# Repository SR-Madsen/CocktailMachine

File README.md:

# Cocktail Machine
Contains the code and PCB used for the actual implementation of the STM32F4-based cocktail machine.

The DiscoveryDemo folder contains a TouchGFX demo used on the STM32F769 Discovery Board from ST.

Documentation, including a system report written in LaTeX, can be found in the Documentation folder.

## Overview
A block diagram overview of the system is shown below.

## Hardware
The PCB has been designed with inspiration from ST's discovery board.

## Software
A preliminary GUI template is shown below. This has been implemented in TouchGFX.

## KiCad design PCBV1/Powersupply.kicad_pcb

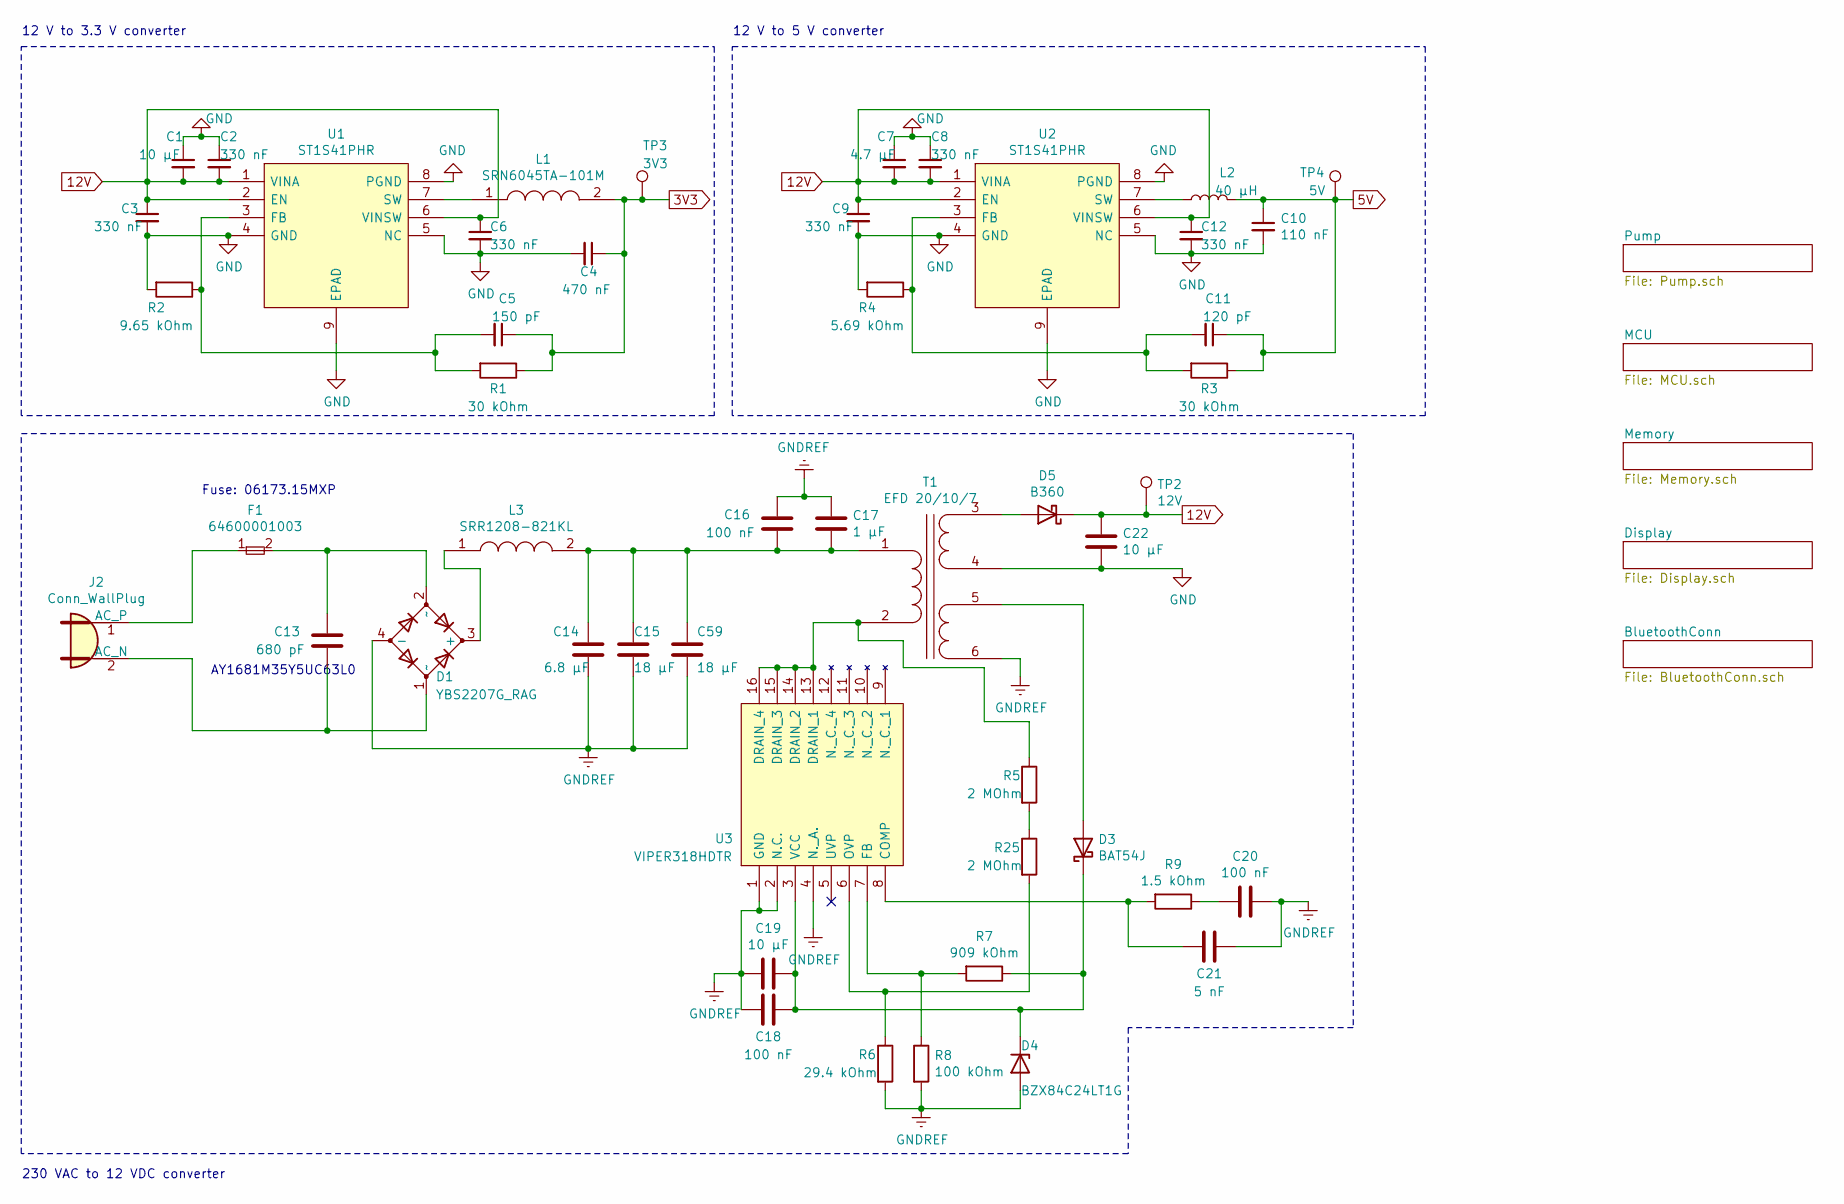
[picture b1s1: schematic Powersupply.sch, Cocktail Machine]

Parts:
C1, C19, C22: 10 µF; C_1206_3216Metric
C2, C3, C6, C8, C9, C12: 330 nF; C_0603_1608Metric
C4: 470 nF; C_0603_1608Metric
C5: 150 pF; C_0603_1608Metric
C7: 4.7 µF; C_0805_2012Metric
C10: 110 nF; C_0603_1608Metric
C11: 120 pF; C_0603_1608Metric
C13: 680 pF; C_Disc_D8.0mm_W5.0mm_P10.00mm
C14: 6.8 µF; CP_Radial_D10.0mm_P5.00mm
C15, C59: 18 µF; CP_Radial_D12.5mm_P5.00mm
C16: 100 nF; C_1210_3225Metric
C17: 1 µF; C_Rect_L24.0mm_W10.1mm_P22.50mm_MKT
C18, C20: 100 nF; C_0603_1608Metric
C21: 5 nF; C_0603_1608Metric
D1: YBS2207G_RAG; Mouser Part Number 821-YBS2207GRAG
D3: BAT54J; D_SOD-323F
D4: BZX84C24LT1G; D_SOT-23_ANK
D5: B360; D_SMC
F1: 64600001003; Mouser Part Number 576-64600001003
J2: Conn_WallPlug; PinHeader_1x02_P2.54mm_Vertical
L1: SRN6045TA-101M; Mouser Part Number 652-SRN6045TA-101M
L2: 40 µH; L_Bourns-SRN4018
L3: SRR1208-821KL; Mouser Part Number 652-SRR1208-821KL
R1, R3: 30 kOhm; R_0603_1608Metric
R2: 9.65 kOhm; R_0603_1608Metric
R4: 5.69 kOhm; R_0603_1608Metric
R5, R25: 2 MOhm; R_1206_3216Metric
R6: 29.4 kOhm; R_0603_1608Metric
R7: 909 kOhm; R_0603_1608Metric
R8: 100 kOhm; R_0603_1608Metric
R9: 1.5 kOhm; R_0603_1608Metric
T1: EFD 20/10/7; EFD_20_10_7
TP2: 12V; TestPoint_Pad_D2.0mm
TP3: 3V3; TestPoint_Pad_D2.0mm
TP4: 5V; TestPoint_Pad_D2.0mm
U1, U2: ST1S41PHR; Manufacturer_Part_Number ST1S41PHR
U3: VIPER318HDTR; Manufacturer_Part_Number VIPER318HDTR

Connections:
3V3: C4.1, C5.1, L1.2, R1.1, TP3.1; also elsewhere on the board
5V: C10.1, C11.1, L2.2, R3.1, TP4.1; also elsewhere on the board
12V: C1.2, C2.2, C3.1, C6.1, C7.2, C8.2, C9.1, C12.1, C22.1, D5.1 (K), TP2.1, U1.1 (VINA), U1.2 (EN), U1.6 (VINSW), U2.1 (VINA), U2.2 (EN), U2.6 (VINSW); also elsewhere on the board
GND: C1.1, C2.1, C3.2, C4.2, C6.2, C7.1, C8.1, C9.2, C10.2, C12.2, C22.2, R2.2, R4.2, T1.4 (SB), U1.4 (GND), U1.5 (NC), U1.8 (PGND), U1.9 (EPAD), U2.4 (GND), U2.5 (NC), U2.8 (PGND), U2.9 (EPAD); also elsewhere on the board
GNDREF: C14.2, C15.2, C16.1, C17.1, C18.2, C19.2, C20.1, C21.1, C59.2, D1.4 (-), D4.2 (A), R6.2, R8.2, T1.6 (SD), U3.1 (GND), U3.2 (N.C.), U3.4 (N._A.)
unnamed: C5.2, R1.2, R2.1, U1.3 (FB)
unnamed: C11.2, R3.2, R4.1, U2.3 (FB)
unnamed: C13.1, D1.2 (~~), F1.2
unnamed: C13.2, D1.1 (~~), J2.2 (AC_N)
unnamed: C14.1, C15.1, C16.2, C17.2, C59.1, L3.2, T1.1 (AA)
unnamed: C18.1, C19.1, D3.1 (K), D4.1 (K), R7.1, U3.3 (VCC)
unnamed: C20.2, R9.1
unnamed: C21.2, R9.2, U3.8 (COMP)
unnamed: D1.3 (+), L3.1
unnamed: D3.2 (A), T1.5 (SC)
unnamed: D5.2 (A), T1.3 (SA)
unnamed: F1.1, J2.1 (AC_P)
unnamed: L1.1, U1.7 (SW)
unnamed: L2.1, U2.7 (SW)
unnamed: R5.1, T1.2 (AB), U3.13 (DRAIN_1), U3.14 (DRAIN_2), U3.15 (DRAIN_3), U3.16 (DRAIN_4)
unnamed: R7.2, R8.1, U3.7 (FB)
unnamed: R5.2, R25.1
unnamed: R6.1, R25.2, U3.6 (OVP)

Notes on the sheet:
12 V to 3.3 V converter
12 V to 5 V converter
Fuse: 06173.15MXP
AY1681M35Y5UC63L0
230 VAC to 12 VDC converter

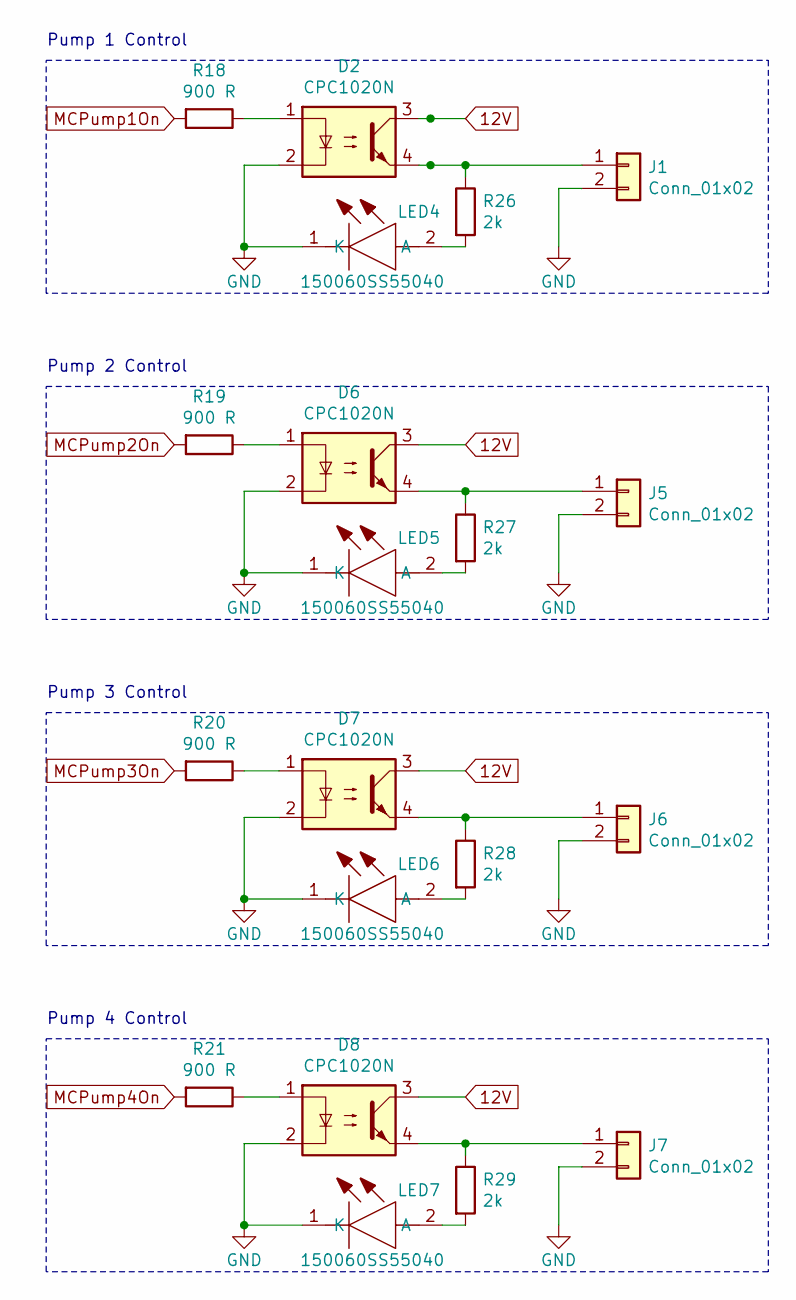
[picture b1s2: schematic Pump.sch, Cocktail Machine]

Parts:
D2, D6, D7, D8: CPC1020N; Mouser Part Number 849-CPC1020N
J1, J5, J6, J7: Conn_01x02; PinHeader_1x02_P2.54mm_Horizontal
LED4, LED5, LED6, LED7: 150060SS55040; Mouser Part Number 710-150060SS55040
R18, R19, R20, R21: 900 R; R_0603_1608Metric
R26, R27, R28, R29: 2k; R_0603_1608Metric

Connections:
12V: D2.3, D6.3, D7.3, D8.3; also elsewhere on the board
GND: D2.2, D6.2, D7.2, D8.2, J1.2, J5.2, J6.2, J7.2, LED4.1 (K), LED5.1 (K), LED6.1 (K), LED7.1 (K); also elsewhere on the board
MCPump1On: R18.2; also elsewhere on the board
MCPump2On: R19.2; also elsewhere on the board
MCPump3On: R20.2; also elsewhere on the board
MCPump4On: R21.2; also elsewhere on the board
unnamed: D2.1, R18.1
unnamed: D2.4, J1.1, R26.1
unnamed: D6.1, R19.1
unnamed: D6.4, J5.1, R27.1
unnamed: D7.1, R20.1
unnamed: D7.4, J6.1, R28.1
unnamed: D8.1, R21.1
unnamed: D8.4, J7.1, R29.1
unnamed: LED4.2 (A), R26.2
unnamed: LED5.2 (A), R27.2
unnamed: LED6.2 (A), R28.2
unnamed: LED7.2 (A), R29.2

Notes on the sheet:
Pump 1 Control
Pump 2 Control
Pump 3 Control
Pump 4 Control

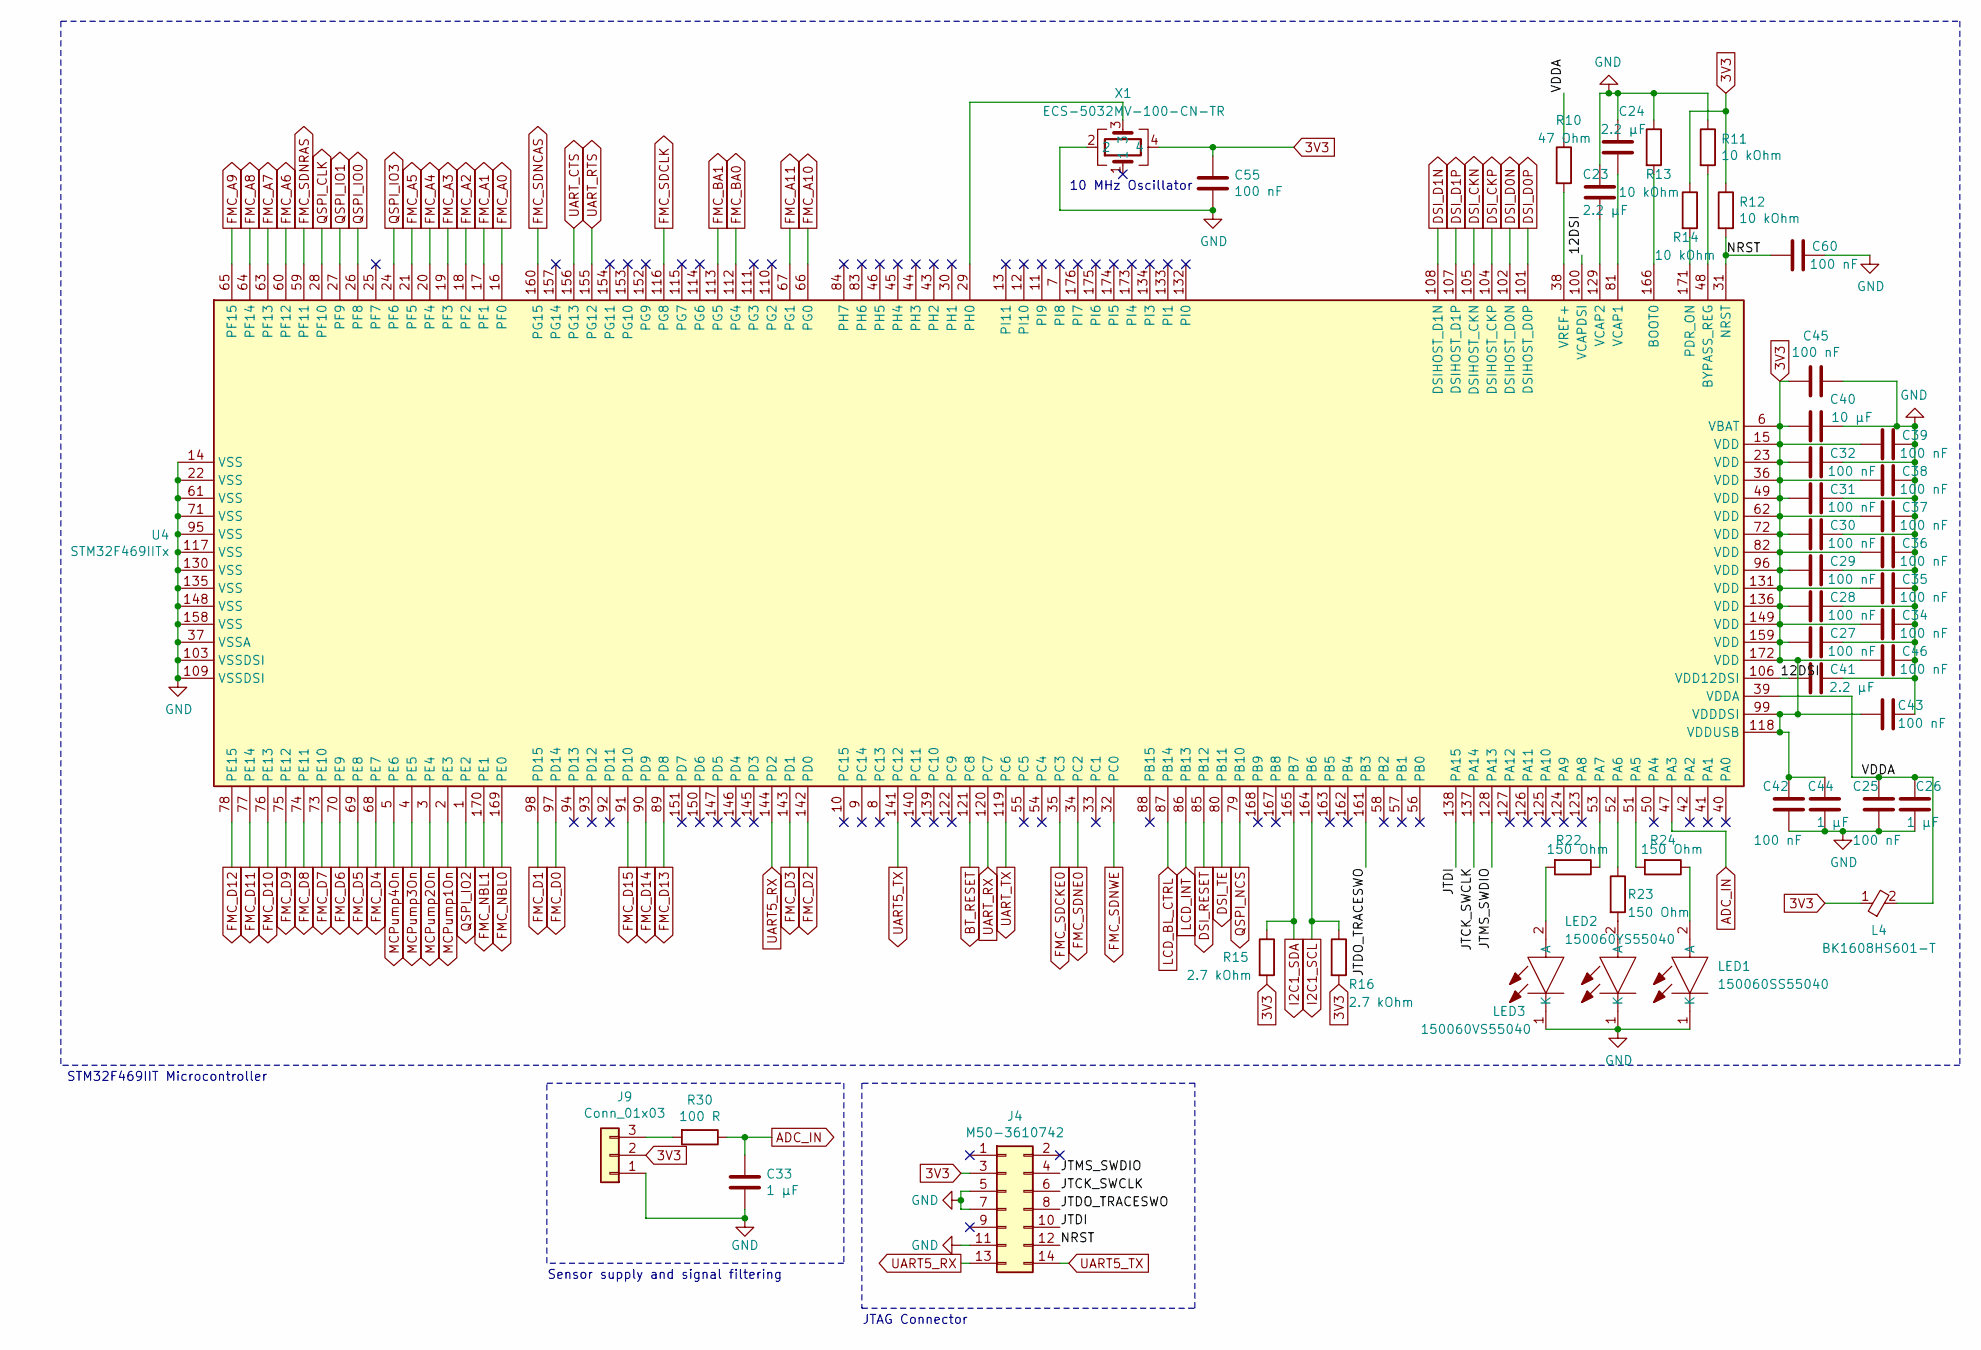
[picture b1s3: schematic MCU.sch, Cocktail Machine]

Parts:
C23, C24, C41: 2.2 µF; C_0603_1608Metric
C25, C27, C28, C29, C30, C31, C32, C34, C35, C36, C37, C38, C39, C42, C43, C45, C46, C55, C60: 100 nF; C_0603_1608Metric
C26, C33, C44: 1 µF; C_0603_1608Metric
C40: 10 µF; C_0603_1608Metric
J4: M50-3610742; M50-3610742R
J9: Conn_01x03; PinHeader_1x03_P2.54mm_Vertical
L4: BK1608HS601-T; Mouser Part Number 963-BK1608HS601-T
LED1: 150060SS55040; Mouser Part Number 710-150060SS55040
LED2: 150060YS55040; 150060VS55040; Mouser Part Number 710-150060YS55040
LED3: 150060VS55040; Mouser Part Number 710-150060VS55040
R10: 47 Ohm; R_0603_1608Metric
R11, R12, R13, R14: 10 kOhm; R_0603_1608Metric
R15, R16: 2.7 kOhm; R_0603_1608Metric
R22, R23, R24: 150 Ohm; R_0603_1608Metric
R30: 100 R; R_0603_1608Metric
U4: STM32F469IITx; LQFP-176_24x24mm_P0.5mm
X1: ECS-5032MV-100-CN-TR; ECS5032MV250CNTR; Mouser Part Number 520-5032MV-250-CNT

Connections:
3V3: C27.2, C28.2, C29.2, C30.2, C31.2, C32.2, C34.2, C35.2, C36.2, C37.2, C38.2, C39.2, C40.2, C42.1, C43.2, C44.1, C45.2, C46.1, C55.1, J4.3, J9.2, L4.1, R12.1, R14.1, R15.2, R16.2, U4.6 (VBAT), U4.15 (VDD), U4.23 (VDD), U4.36 (VDD), U4.49 (VDD), U4.62 (VDD), U4.72 (VDD), U4.82 (VDD), U4.96 (VDD), U4.99 (VDDDSI), U4.118 (VDDUSB), U4.131 (VDD), U4.136 (VDD), U4.149 (VDD), U4.159 (VDD), U4.172 (VDD), X1.4; also elsewhere on the board
/MCU/12DSI: C41.2, U4.100 (VCAPDSI), U4.106 (VDD12DSI)
/MCU/JTCK_SWCLK: J4.6, U4.137 (PA14)
/MCU/JTDI: J4.10, U4.138 (PA15)
/MCU/JTDO_TRACESWO: J4.8, U4.161 (PB3)
/MCU/JTMS_SWDIO: J4.4, U4.128 (PA13)
/MCU/NRST: C60.2, J4.12, R12.2, U4.31 (NRST)
/MCU/VDDA: C25.1, C26.1, L4.2, R10.1, U4.39 (VDDA)
ADC_IN: C33.1, R30.1, U4.47 (PA3)
BT_RESET: U4.121 (PC8); also elsewhere on the board
DSI_CKN: U4.105 (DSIHOST_CKN); also elsewhere on the board
DSI_CKP: U4.104 (DSIHOST_CKP); also elsewhere on the board
DSI_D0N: U4.102 (DSIHOST_D0N); also elsewhere on the board
DSI_D0P: U4.101 (DSIHOST_D0P); also elsewhere on the board
DSI_D1N: U4.108 (DSIHOST_D1N); also elsewhere on the board
DSI_D1P: U4.107 (DSIHOST_D1P); also elsewhere on the board
DSI_RESET: U4.85 (PB12); also elsewhere on the board
DSI_TE: U4.80 (PB11); also elsewhere on the board
FMC_A0: U4.16 (PF0); also elsewhere on the board
FMC_A1: U4.17 (PF1); also elsewhere on the board
FMC_A2: U4.18 (PF2); also elsewhere on the board
FMC_A3: U4.19 (PF3); also elsewhere on the board
FMC_A4: U4.20 (PF4); also elsewhere on the board
FMC_A5: U4.21 (PF5); also elsewhere on the board
FMC_A6: U4.60 (PF12); also elsewhere on the board
FMC_A7: U4.63 (PF13); also elsewhere on the board
FMC_A8: U4.64 (PF14); also elsewhere on the board
FMC_A9: U4.65 (PF15); also elsewhere on the board
FMC_A10: U4.66 (PG0); also elsewhere on the board
FMC_A11: U4.67 (PG1); also elsewhere on the board
FMC_BA0: U4.112 (PG4); also elsewhere on the board
FMC_BA1: U4.113 (PG5); also elsewhere on the board
FMC_D0: U4.97 (PD14); also elsewhere on the board
FMC_D1: U4.98 (PD15); also elsewhere on the board
FMC_D2: U4.142 (PD0); also elsewhere on the board
FMC_D3: U4.143 (PD1); also elsewhere on the board
FMC_D4: U4.68 (PE7); also elsewhere on the board
FMC_D5: U4.69 (PE8); also elsewhere on the board
FMC_D6: U4.70 (PE9); also elsewhere on the board
FMC_D7: U4.73 (PE10); also elsewhere on the board
FMC_D8: U4.74 (PE11); also elsewhere on the board
FMC_D9: U4.75 (PE12); also elsewhere on the board
FMC_D10: U4.76 (PE13); also elsewhere on the board
FMC_D11: U4.77 (PE14); also elsewhere on the board
FMC_D12: U4.78 (PE15); also elsewhere on the board
FMC_D13: U4.89 (PD8); also elsewhere on the board
FMC_D14: U4.90 (PD9); also elsewhere on the board
FMC_D15: U4.91 (PD10); also elsewhere on the board
FMC_NBL0: U4.169 (PE0); also elsewhere on the board
FMC_NBL1: U4.170 (PE1); also elsewhere on the board
FMC_SDCKE0: U4.35 (PC3); also elsewhere on the board
FMC_SDCLK: U4.116 (PG8); also elsewhere on the board
FMC_SDNCAS: U4.160 (PG15); also elsewhere on the board
FMC_SDNE0: U4.34 (PC2); also elsewhere on the board
FMC_SDNRAS: U4.59 (PF11); also elsewhere on the board
FMC_SDNWE: U4.32 (PC0); also elsewhere on the board
GND: C23.1, C24.1, C25.2, C26.2, C27.1, C28.1, C29.1, C30.1, C31.1, C32.1, C33.2, C34.1, C35.1, C36.1, C37.1, C38.1, C39.1, C40.1, C41.1, C42.2, C43.1, C44.2, C45.1, C46.2, C55.2, C60.1, J4.5, J4.7, J4.11, J9.1, LED1.1 (K), LED2.1 (K), LED3.1 (K), R11.1, R13.1, U4.14 (VSS), U4.22 (VSS), U4.37 (VSSA), U4.61 (VSS), U4.71 (VSS), U4.95 (VSS), U4.103 (VSSDSI), U4.109 (VSSDSI), U4.117 (VSS), U4.130 (VSS), U4.135 (VSS), U4.148 (VSS), U4.158 (VSS), X1.2; also elsewhere on the board
I2C1_SCL: R16.1, U4.164 (PB6); also elsewhere on the board
I2C1_SDA: R15.1, U4.165 (PB7); also elsewhere on the board
LCD_BL_CTRL: U4.87 (PB14); also elsewhere on the board
LCD_INT: U4.86 (PB13); also elsewhere on the board
MCPump1On: U4.2 (PE3); also elsewhere on the board
MCPump2On: U4.3 (PE4); also elsewhere on the board
MCPump3On: U4.4 (PE5); also elsewhere on the board
MCPump4On: U4.5 (PE6); also elsewhere on the board
unnamed: C23.2, U4.129 (VCAP2)
unnamed: C24.2, U4.81 (VCAP1)
unnamed: J9.3, R30.2
unnamed: LED1.2 (A), R24.1
unnamed: LED2.2 (A), R23.2
unnamed: LED3.2 (A), R22.2
unnamed: R10.2, U4.38 (VREF+)
unnamed: R11.2, U4.48 (BYPASS_REG)
unnamed: R13.2, U4.166 (BOOT0)
unnamed: R14.2, U4.171 (PDR_ON)
unnamed: R22.1, U4.53 (PA7)
unnamed: R23.1, U4.52 (PA6)
unnamed: R24.2, U4.51 (PA5)
unnamed: U4.29 (PH0), X1.3
QSPI_CLK: U4.28 (PF10); also elsewhere on the board
QSPI_IO0: U4.26 (PF8); also elsewhere on the board
QSPI_IO1: U4.27 (PF9); also elsewhere on the board
QSPI_IO2: U4.1 (PE2); also elsewhere on the board
QSPI_IO3: U4.24 (PF6); also elsewhere on the board
QSPI_NCS: U4.79 (PB10); also elsewhere on the board
UART5_RX: J4.13, U4.144 (PD2)
UART5_TX: J4.14, U4.141 (PC12)
UART_CTS: U4.156 (PG13); also elsewhere on the board
UART_RTS: U4.155 (PG12); also elsewhere on the board
UART_RX: U4.120 (PC7); also elsewhere on the board
UART_TX: U4.119 (PC6); also elsewhere on the board

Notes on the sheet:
JTAG Connector
STM32F469IIT Microcontroller
10 MHz Oscillator
Sensor supply and signal filtering

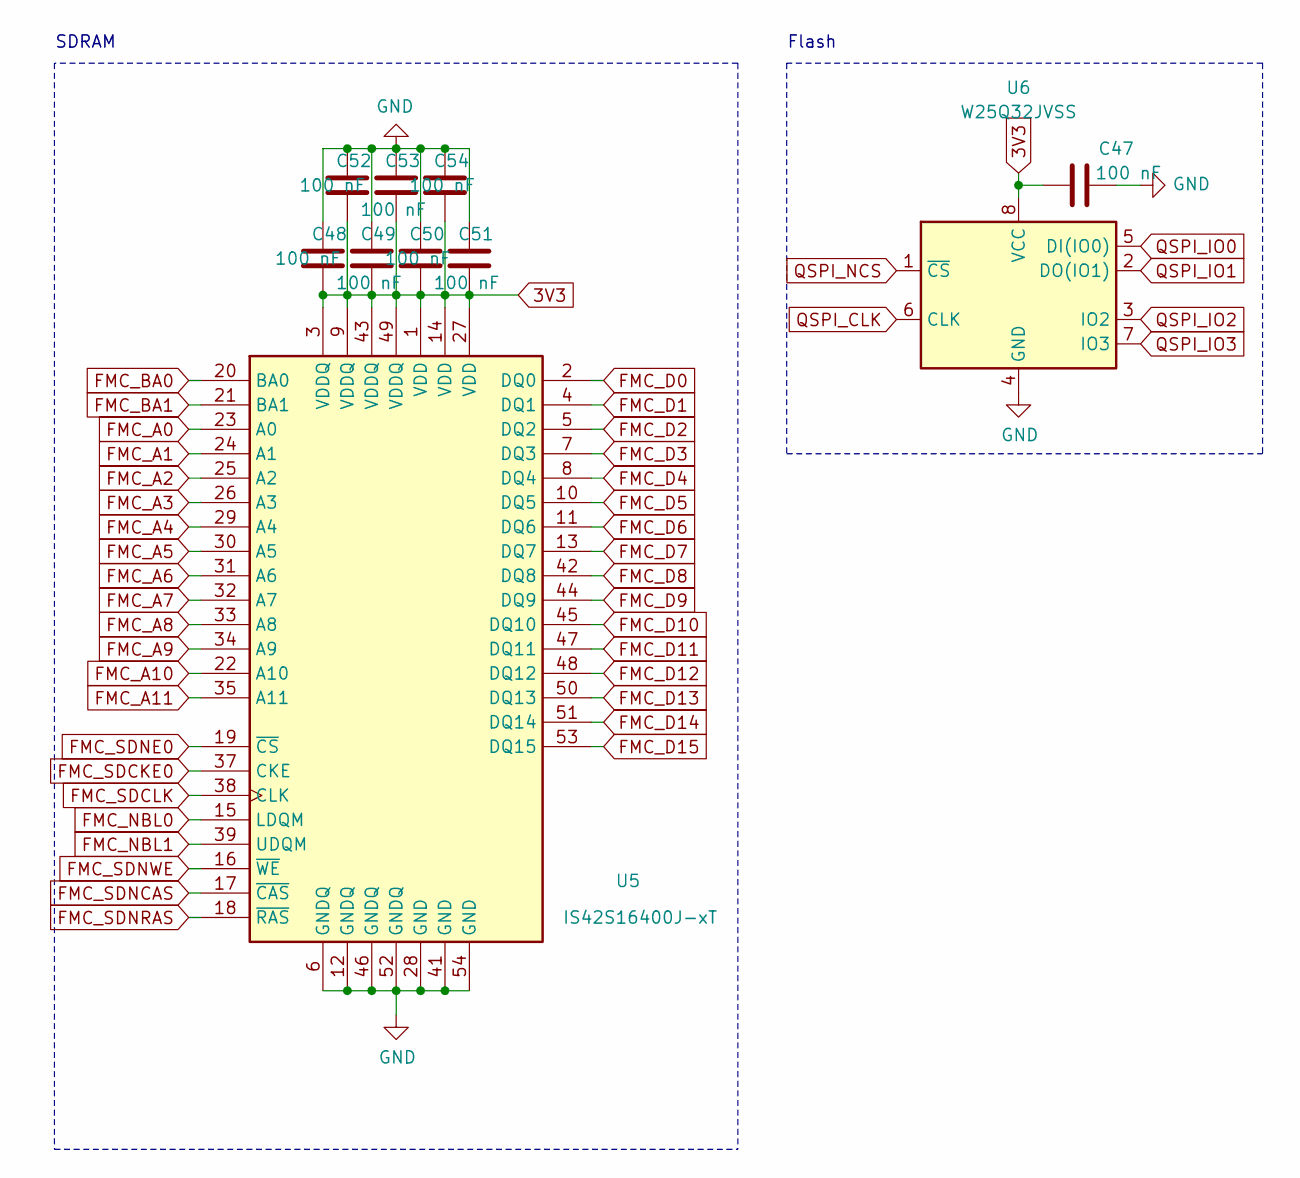
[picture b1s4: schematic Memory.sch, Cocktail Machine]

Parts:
C47, C48, C49, C50, C51, C52, C53, C54: 100 nF; C_0603_1608Metric
U5: IS42S16400J-xT; TSOP-II-54_22.2x10.16mm_P0.8mm
U6: W25Q32JVSS; SOIC-8_5.23x5.23mm_P1.27mm

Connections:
3V3: C47.2, C48.2, C49.2, C50.2, C51.2, C52.2, C53.2, C54.2, U5.1 (VDD), U5.3 (VDDQ), U5.9 (VDDQ), U5.14 (VDD), U5.27 (VDD), U5.43 (VDDQ), U5.49 (VDDQ), U6.8 (VCC); also elsewhere on the board
FMC_A0: U5.23 (A0); also elsewhere on the board
FMC_A1: U5.24 (A1); also elsewhere on the board
FMC_A2: U5.25 (A2); also elsewhere on the board
FMC_A3: U5.26 (A3); also elsewhere on the board
FMC_A4: U5.29 (A4); also elsewhere on the board
FMC_A5: U5.30 (A5); also elsewhere on the board
FMC_A6: U5.31 (A6); also elsewhere on the board
FMC_A7: U5.32 (A7); also elsewhere on the board
FMC_A8: U5.33 (A8); also elsewhere on the board
FMC_A9: U5.34 (A9); also elsewhere on the board
FMC_A10: U5.22 (A10); also elsewhere on the board
FMC_A11: U5.35 (A11); also elsewhere on the board
FMC_BA0: U5.20 (BA0); also elsewhere on the board
FMC_BA1: U5.21 (BA1); also elsewhere on the board
FMC_D0: U5.2 (DQ0); also elsewhere on the board
FMC_D1: U5.4 (DQ1); also elsewhere on the board
FMC_D2: U5.5 (DQ2); also elsewhere on the board
FMC_D3: U5.7 (DQ3); also elsewhere on the board
FMC_D4: U5.8 (DQ4); also elsewhere on the board
FMC_D5: U5.10 (DQ5); also elsewhere on the board
FMC_D6: U5.11 (DQ6); also elsewhere on the board
FMC_D7: U5.13 (DQ7); also elsewhere on the board
FMC_D8: U5.42 (DQ8); also elsewhere on the board
FMC_D9: U5.44 (DQ9); also elsewhere on the board
FMC_D10: U5.45 (DQ10); also elsewhere on the board
FMC_D11: U5.47 (DQ11); also elsewhere on the board
FMC_D12: U5.48 (DQ12); also elsewhere on the board
FMC_D13: U5.50 (DQ13); also elsewhere on the board
FMC_D14: U5.51 (DQ14); also elsewhere on the board
FMC_D15: U5.53 (DQ15); also elsewhere on the board
FMC_NBL0: U5.15 (LDQM); also elsewhere on the board
FMC_NBL1: U5.39 (UDQM); also elsewhere on the board
FMC_SDCKE0: U5.37 (CKE); also elsewhere on the board
FMC_SDCLK: U5.38 (CLK); also elsewhere on the board
FMC_SDNCAS: U5.17 (~CAS); also elsewhere on the board
FMC_SDNE0: U5.19 (~CS); also elsewhere on the board
FMC_SDNRAS: U5.18 (~RAS); also elsewhere on the board
FMC_SDNWE: U5.16 (~WE); also elsewhere on the board
GND: C47.1, C48.1, C49.1, C50.1, C51.1, C52.1, C53.1, C54.1, U5.6 (GNDQ), U5.12 (GNDQ), U5.28 (GND), U5.41 (GND), U5.46 (GNDQ), U5.52 (GNDQ), U5.54 (GND), U6.4 (GND); also elsewhere on the board
QSPI_CLK: U6.6 (CLK); also elsewhere on the board
QSPI_IO0: U6.5 (DI(IO0)); also elsewhere on the board
QSPI_IO1: U6.2 (DO(IO1)); also elsewhere on the board
QSPI_IO2: U6.3 (IO2); also elsewhere on the board
QSPI_IO3: U6.7 (IO3); also elsewhere on the board
QSPI_NCS: U6.1 (~CS); also elsewhere on the board

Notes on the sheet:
SDRAM
Flash

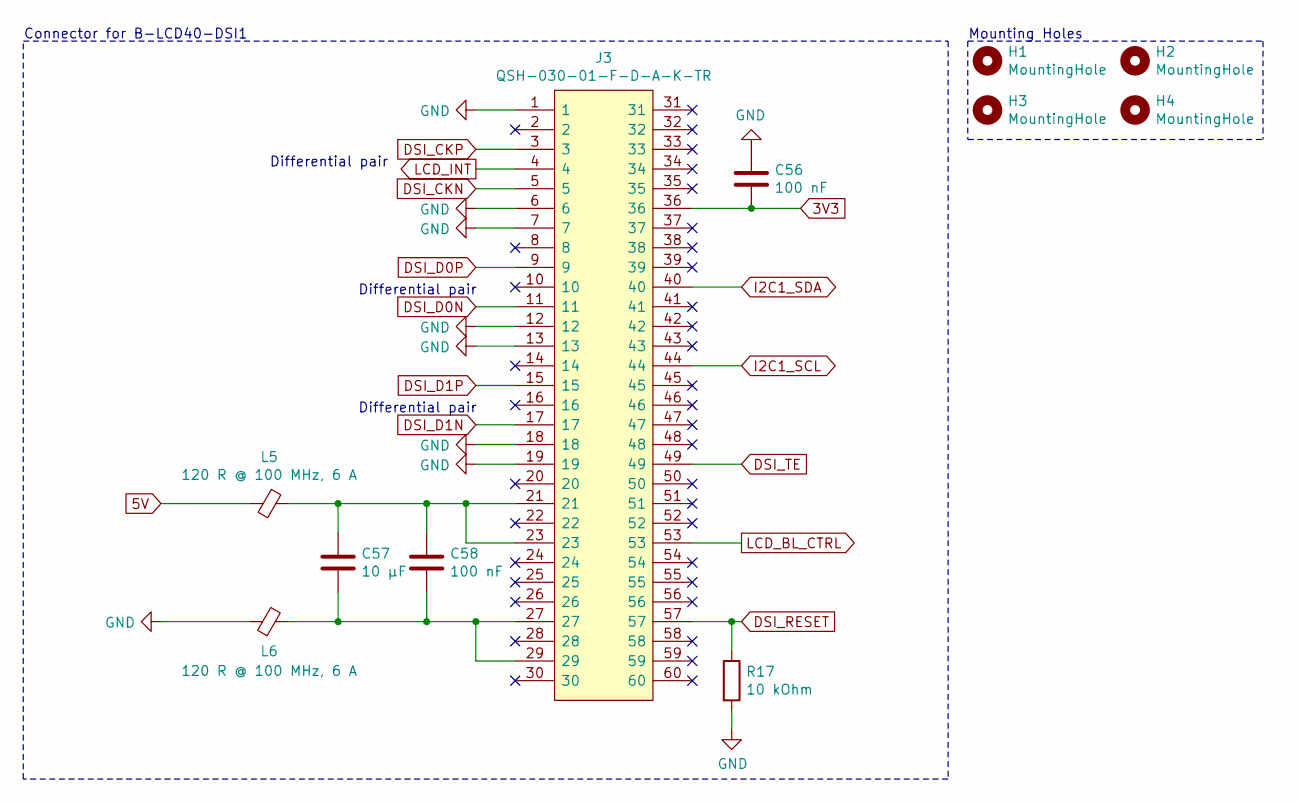
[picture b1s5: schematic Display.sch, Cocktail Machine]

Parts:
C56, C58: 100 nF; C_0603_1608Metric
C57: 10 µF; C_1206_3216Metric
H1, H2, H3, H4: MountingHole; MountingHole_6.4mm_M6_DIN965
J3: QSH-030-01-F-D-A-K-TR; QSH-030-01-F-D-A; Mouser Part Number 200-QSH03001FDAKTR
L5, L6: 120 R @ 100 MHz, 6 A; L_0805_2012Metric
R17: 10 kOhm; R_0603_1608Metric

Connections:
3V3: C56.2, J3.36; also elsewhere on the board
5V: L5.2; also elsewhere on the board
DSI_CKN: J3.5; also elsewhere on the board
DSI_CKP: J3.3; also elsewhere on the board
DSI_D0N: J3.11; also elsewhere on the board
DSI_D0P: J3.9; also elsewhere on the board
DSI_D1N: J3.17; also elsewhere on the board
DSI_D1P: J3.15; also elsewhere on the board
DSI_RESET: J3.57, R17.1; also elsewhere on the board
DSI_TE: J3.49; also elsewhere on the board
GND: C56.1, J3.1, J3.6, J3.7, J3.12, J3.13, J3.18, J3.19, L6.1, R17.2; also elsewhere on the board
I2C1_SCL: J3.44; also elsewhere on the board
I2C1_SDA: J3.40; also elsewhere on the board
LCD_BL_CTRL: J3.53; also elsewhere on the board
LCD_INT: J3.4; also elsewhere on the board
unnamed: C57.1, C58.1, J3.21, J3.23, L5.1
unnamed: C57.2, C58.2, J3.27, J3.29, L6.2

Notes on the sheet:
Connector for B-LCD40-DSI1
Mounting Holes
Differential pair

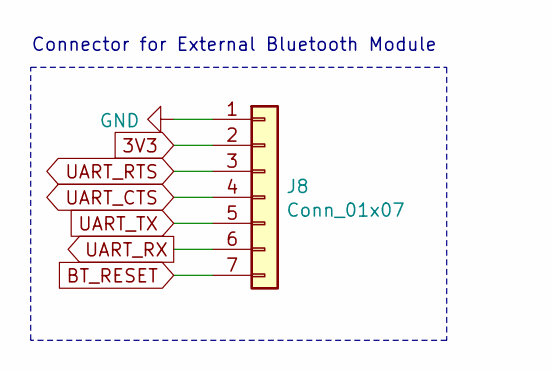
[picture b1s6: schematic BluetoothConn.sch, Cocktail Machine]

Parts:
J8: Conn_01x07; PinHeader_1x07_P2.54mm_Vertical

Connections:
3V3: J8.2; also elsewhere on the board
BT_RESET: J8.7; also elsewhere on the board
GND: J8.1; also elsewhere on the board
UART_CTS: J8.4; also elsewhere on the board
UART_RTS: J8.3; also elsewhere on the board
UART_RX: J8.6; also elsewhere on the board
UART_TX: J8.5; also elsewhere on the board

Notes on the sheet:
Connector for External Bluetooth Module

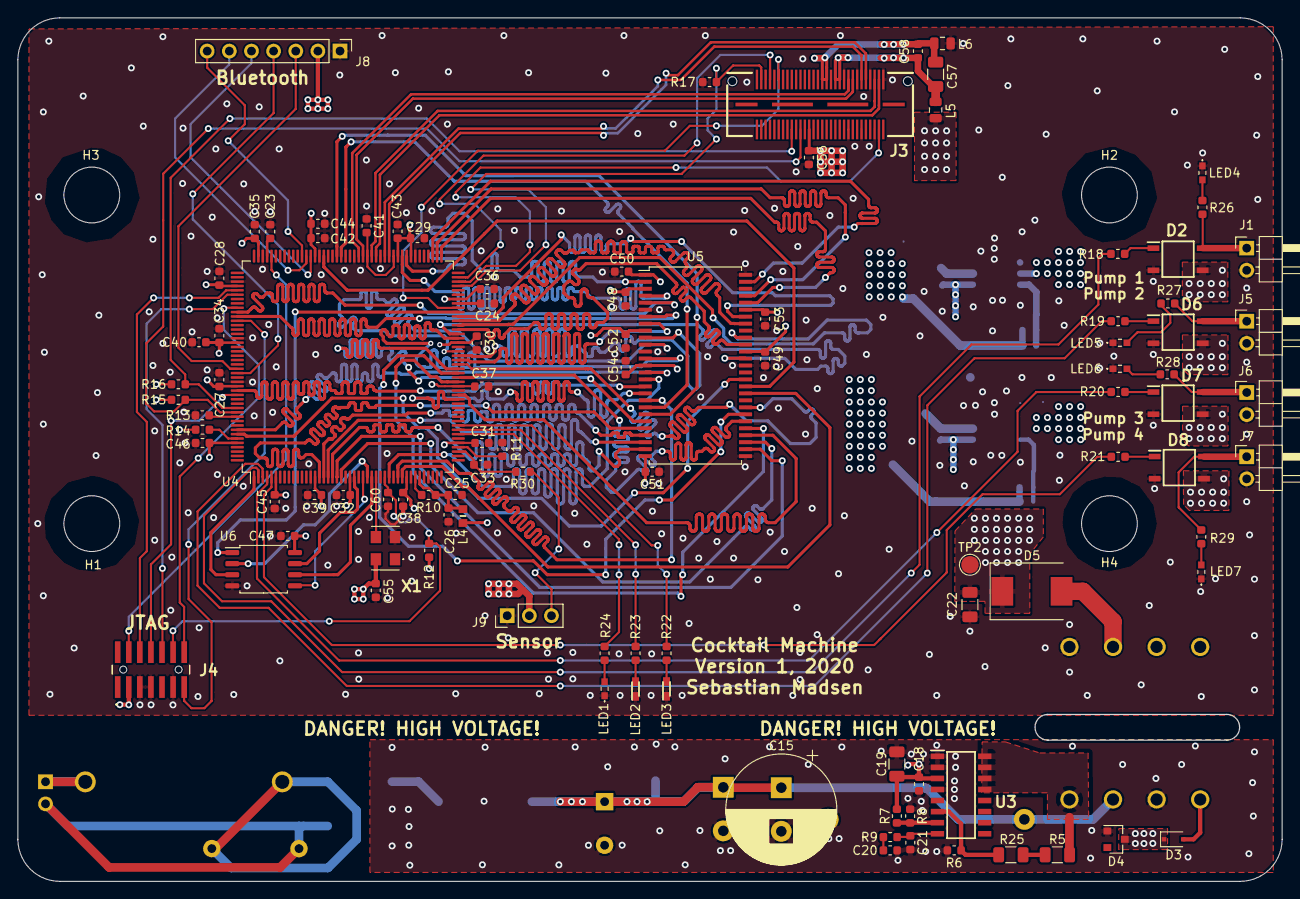
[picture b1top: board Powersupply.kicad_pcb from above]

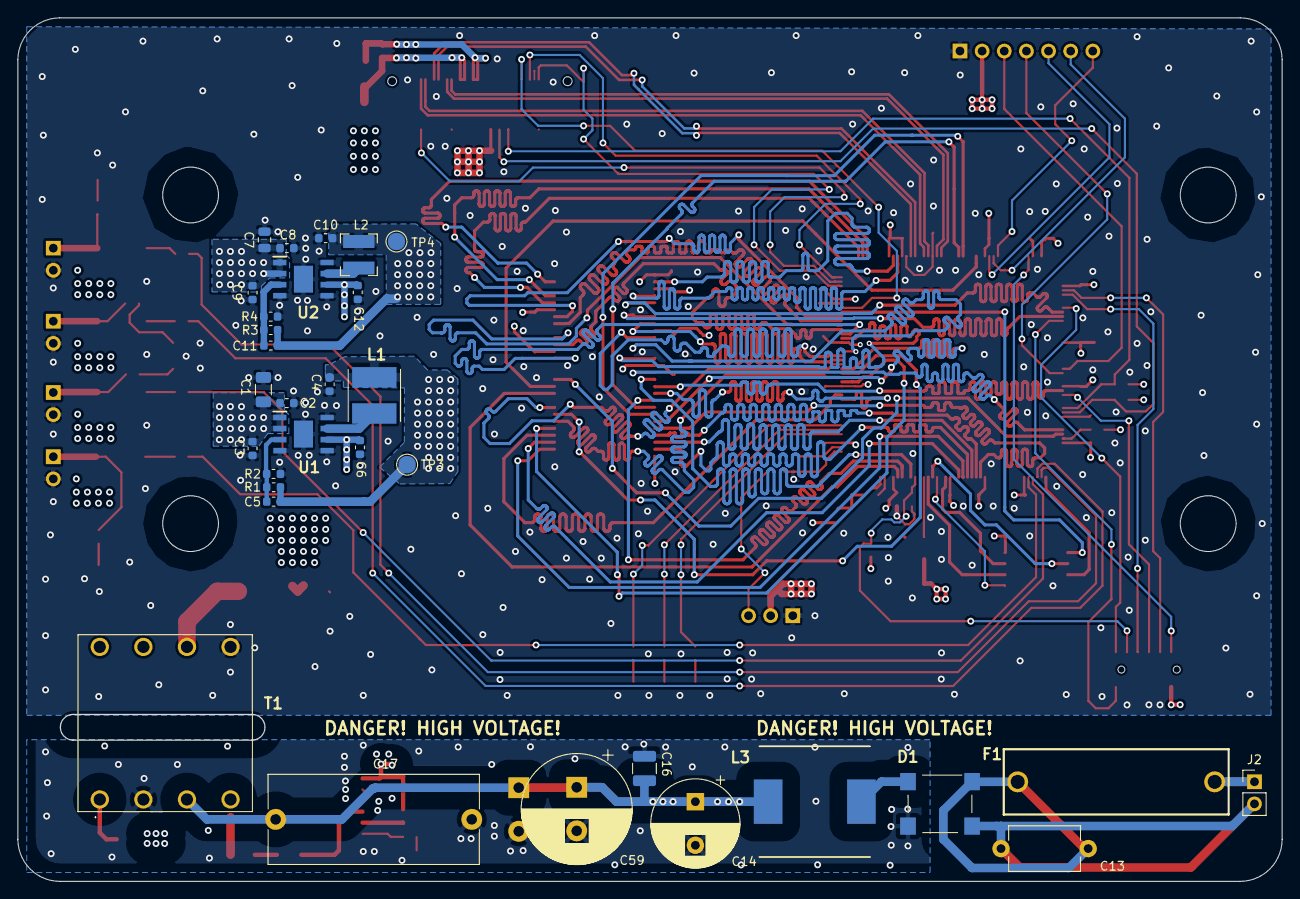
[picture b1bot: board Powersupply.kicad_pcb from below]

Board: 4 copper layers, 145.0 x 99.1 mm, 136 parts (32 on the bottom side), 126 nets.

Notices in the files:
Software/Core/Src/stm32f4xx_hal_msp.c:
© Copyright (c) 2021 STMicroelectronics.
All rights reserved.
This software component is licensed by ST under Ultimate Liberty license
(C) COPYRIGHT STMicroelectronics *****END OF FILE
